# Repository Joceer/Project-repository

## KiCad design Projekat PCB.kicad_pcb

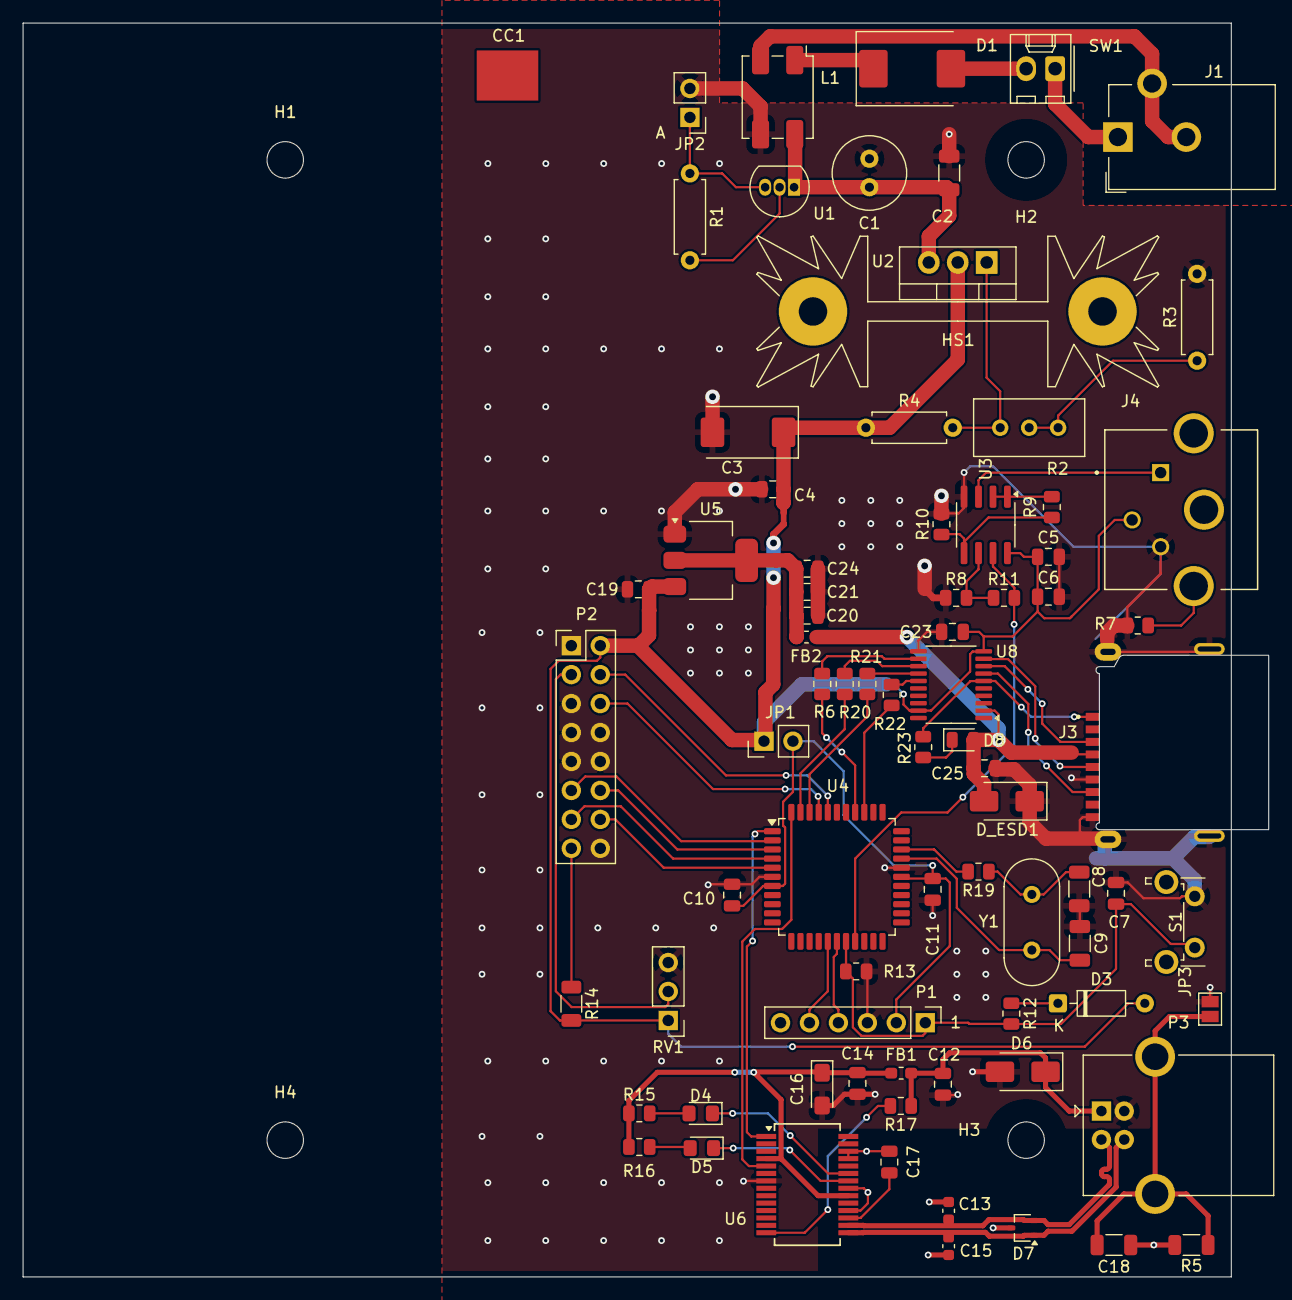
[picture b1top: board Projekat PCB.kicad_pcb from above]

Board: 2 copper layers, 109.3 x 109.9 mm, 84 parts (0 on the bottom side), 62 nets.

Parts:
C1: 100u/25V; C_Radial_D6.3mm_H11.0mm_P2.50mm
C2: 100n; C_1206_3216Metric
C3: 220u/10V Tantalum; CP_EIA-7343-43_Kemet-X
C4, C5, C6, C7, C10, C11, C14, C17: 100n; C_0805_2012Metric
C8, C9: 22p; C_1206_3216Metric
C12: 10n; C_0805_2012Metric
C13, C15: 47p; C_0603_1608Metric
C16: 4u7/10V Tantalum; CP_EIA-3216-18_Kemet-A_Pad1.58x1.35mm_HandSolder
C18: TBD; C_1206_3216Metric
C19, C20: 10uF; C_0805_2012Metric
C21, C23, C25: 100nF; C_0805_2012Metric
C24: 10nF; C_0805_2012Metric
CC1: Cable Clip S8101-46R; S8101-46R
D1: S3B-E3/57T; D_SMC
D3: BAT43; D_DO-35_SOD27_P7.62mm_Horizontal
D4: Green; LED_0805_2012Metric_Pad1.15x1.40mm_HandSolder
D5: Red; LED_0805_2012Metric_Pad1.15x1.40mm_HandSolder
D6: P4SMA6.8CA; D_SMA
D7: ESD7002; SOT-323_SC-70
D8: LED; LED_0805_2012Metric
D_ESD1: PESD3V3L1BA; D_SMA
FB1, FB2: BLM18PG330SN1; L_0603_1608Metric_Pad1.05x0.95mm_HandSolder
H1, H2, H3, H4: MountingHole; MountingHole_3.2mm_M3
HS1: Heatsink_Pad_2Pin; Heatsink_Fischer_SK104-STC-STIC_35x13mm_2xDrill2.5mm
J1: PJ-002A; BarrelJack_CUI_PJ-102AH_Horizontal
J3: MSD-3-A MicroSD card socket; CUI_MSD-3-A
J4: MD-30SM; CUI_MD-30SM
JP1: Jumper; PinHeader_1x02_P2.54mm_Vertical
JP2: Power LED; PinHeader_1x02_P2.54mm_Vertical
JP3: SolderJumper Open; SolderJumper-2_P1.3mm_Open_Pad1.0x1.5mm
L1: ACM7060-701-2PL; L_CommonModeChoke_TDK_ACM7060
NT1: NetTie_2; NetTie-2_SMD_Pad0.5mm
P1: ICSP; PinHeader_1x06_P2.54mm_Vertical
P2: LCD-H; ZP_Flipped_PinSocket_2x08_P2.54mm_Vertical
P3: USB_B; USB_B_OST_USB-B1HSxx_Horizontal
R1: 10R 1%; R_Axial_DIN0207_L6.3mm_D2.5mm_P7.62mm_Horizontal
R2: 500R; Potentiometer_Bourns_3296W_Vertical
R3, R4: 240R 1%; R_Axial_DIN0207_L6.3mm_D2.5mm_P7.62mm_Horizontal
R5: TBD; R_1206_3216Metric
R6, R20, R21, R22, R23: 1k; R_0805_2012Metric
R7: 0R; R_0805_2012Metric
R8, R9: 20k 1%; R_0805_2012Metric
R10, R11: 100k 1%; R_0805_2012Metric
R12: 4k7; R_0805_2012Metric
R13: 100k; R_0805_2012Metric
R14: 10R 1/2W; R_1206_3216Metric
R15, R16: 270R; R_0805_2012Metric
R17: 10k; R_0805_2012Metric
R19: TBD; R_0805_2012Metric
RV1: 10k; PinHeader_1x03_P2.54mm_Vertical
S1: SW_Push; SW_Tactile_SPST_Angled_PTS645Vx58-2LFS
SW1: SW_SPST; Molex_KK-254_AE-6410-02A_1x02_P2.54mm_Vertical
U1: LM334Z; TO-92_Inline
U2: LM317T_TO220; TO-220-3_Vertical
U3: MCP6022-I/SN; SOIC-8_3.9x4.9mm_P1.27mm
U4: PIC18F4520-E/PT; TQFP-44_10x10mm_P0.8mm
U5: AMS1117-3.3; SOT-223-3_TabPin2
U6: FT232RNL; SSOP-28_5.3x10.2mm_P0.65mm
U8: TXS0108EPW; TSSOP-20_4.4x6.5mm_P0.65mm
Y1: 10MHz; Crystal_HC49-U_Vertical

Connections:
/MicroSD card reader/3.3V: C25.1, D8.2 (A), D_ESD1.2 (A2), FB2.2, J3.4 (VDD), U8.2 (VCCA)
/MicroSD card reader/CLK: R6.1, U4.37 (SCK/SCL/RC3)
/MicroSD card reader/CS: R22.1, U4.36 (CCP1/RC2)
/MicroSD card reader/MISO: R21.1, U4.42 (SDI/SDA/RC4)
/MicroSD card reader/MOSI: R20.1, U4.43 (SDO/RC5)
/Microcontroller/DB4: P2.11, U4.2 (PSP4/RD4)
/Microcontroller/DB5: P2.12, U4.3 (PSP5/RD5)
/Microcontroller/DB6: P2.13, U4.4 (PSP6/RD6)
/Microcontroller/DB7: P2.14, U4.5 (PSP7/RD7)
/Microcontroller/PIC_RX: U4.1 (DT/RX/RC7), U6.1 (TXD)
/Microcontroller/PIC_TX: U4.44 (CK/TX/RC6), U6.5 (RXD)
/Microcontroller/S_OUT: R11.2, U3.7, U4.19 (RA0/AN0)
/Microcontroller/VPP: C7.1, P1.1, R12.2, R13.1, S1.2, U4.18 (~MCLR/Vpp)
/Power/VAA: C3.1, C4.1, NT1.1, R4.1, U2.2 (VO)
/Power/VIN: C1.1, C2.1, L1.4, U1.1, U2.3 (VI)
/Sensor/S_IN: J4.1, U3.3 (+)
/USB/USB_D_+: C15.1, D7.1 (K), P3.3 (D+), U6.15 (USBD+)
/USB/USB_D_-: C13.1, D7.2 (K), P3.2 (D-), U6.16 (USBD-)
GND: C1.2, C2.2, C3.2, C4.2, C5.2, C6.2, C7.2, C8.2, C9.2, C10.2, C11.2, C12.2, C13.2, C14.2, C15.2, C16.2, C17.2, C18.2, C19.2, C20.2, C21.2, C23.2, C24.2, C25.2, D6.2 (A2), D7.3 (A), D_ESD1.1 (A1), J3.6 (VSS), J3.CD, J3.G1 (COVER_GND), J3.G2 (COVER_GND), J3.G3 (COVER_GND), J3.G4 (COVER_GND), J4.2, JP2.2 (B), JP3.2 (B), L1.3, P1.3, P2.1, P2.5, P2.7, P2.8, P2.9, P2.10, P2.16, P3.4 (GND), R3.2, R5.2, R7.2, R8.1, R10.2, R13.2, RV1.3, S1.1, U3.4 (V-), U4.6 (VSS), U4.29 (VSS), U5.1 (GND), U6.7 (GND), U6.18 (GND), U6.21 (GND), U6.25 (AGND), U6.26 (TEST), U8.11 (GND)
unnamed: D1.2 (A), SW1.2 (B)
unnamed: D1.1 (K), L1.1
unnamed: D3.1 (K), R12.1
unnamed: D4.2 (A), R15.2
unnamed: D4.1 (K), U6.23 (CBUS0)
unnamed: D5.2 (A), R16.2
unnamed: D5.1 (K), U6.22 (CBUS1)
unnamed: D8.1 (K), R23.1
unnamed: J1.2, J1.3, L1.2
unnamed: J3.5 (CLK), U8.9 (A8)
unnamed: J3.3 (CMD), U8.8 (A7)
unnamed: J3.7 (DAT0), U8.7 (A6)
unnamed: J3.1 (DAT2), R23.2, U8.6 (A5)
unnamed: J4.S2 (SHIELD), R7.1
unnamed: JP2.1 (A), R1.2, U1.3
unnamed: C18.1, JP3.1 (A), P3.5 (Shield), R5.1
unnamed: P1.4, U4.17 (RB7/PGD)
unnamed: P1.5, U4.16 (RB6/PGC)
unnamed: P2.3, RV1.2
unnamed: P2.4, U4.40 (PSP2/RD2)
unnamed: P2.6, U4.41 (PSP3/RD3)
unnamed: P2.15, R14.1
unnamed: R1.1, U1.2
unnamed: R2.2, R2.3, R3.1
unnamed: C8.1, R19.1 (A), Y1.2
unnamed: R19.2 (B), U4.31 (RA6/OSC2/CLKO)
unnamed: J1.1, SW1.1 (A)
unnamed: R2.1, R4.2, U2.1 (ADJ)
unnamed: R9.1, U3.1, U3.2 (-)
unnamed: R9.2, R10.1, U3.5 (+)
unnamed: R8.2, R11.1, U3.6 (-)
unnamed: C9.1, U4.30 (OSC1/CLKI), Y1.1
unnamed: C20.1, C21.1, C24.1, FB2.1, U5.2 (VO)
unnamed: C17.1, U6.17 (3V3OUT)
unnamed: R17.2, U6.14 (CBUS3)
unnamed: R22.2, U8.15 (B5)
unnamed: R21.2, U8.14 (B6)
unnamed: R20.2, U8.13 (B7)
unnamed: R6.2, U8.12 (B8)
VBUS: C12.1, D6.1 (A1), FB1.1, P3.1 (VBUS), R17.1
VCC: C5.1, C6.1, C19.1, C23.1, D3.2 (A), J4.3, JP1.1 (A), NT1.2, P2.2, R14.2, RV1.1, U3.8 (V+), U5.3 (VI), U8.10 (OE), U8.19 (VCCB)
VCCIO: C14.1, C16.1, FB1.2, R15.1, R16.1, U6.4 (VCCIO), U6.20 (VCC)
VDD: C10.1, C11.1, JP1.2 (B), P1.2, U4.7 (VDD), U4.28 (VDD)

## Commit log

2025-07-31 Početna verzija
2025-08-08 Zaključan footprint SDcard socketa na ploči
2025-08-22 proba
2025-08-23 Commit početak
2025-08-24 Dodavanje stiching via
2025-08-24 Pomerene vije
2025-08-28 Zamena Buffer-a sa LevelShifter-om
2025-08-28 Ubacivanje biblioteke LevelShifter-a
2025-09-02 Popravka rutiranja Level Shifter-a
2025-09-03 gitignore
